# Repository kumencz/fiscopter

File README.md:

fiscopter
=========

Eagle: http://www.uloz.to/xudp2hTk/cadsoft-eagle-professional-6-5-0-patch-rar

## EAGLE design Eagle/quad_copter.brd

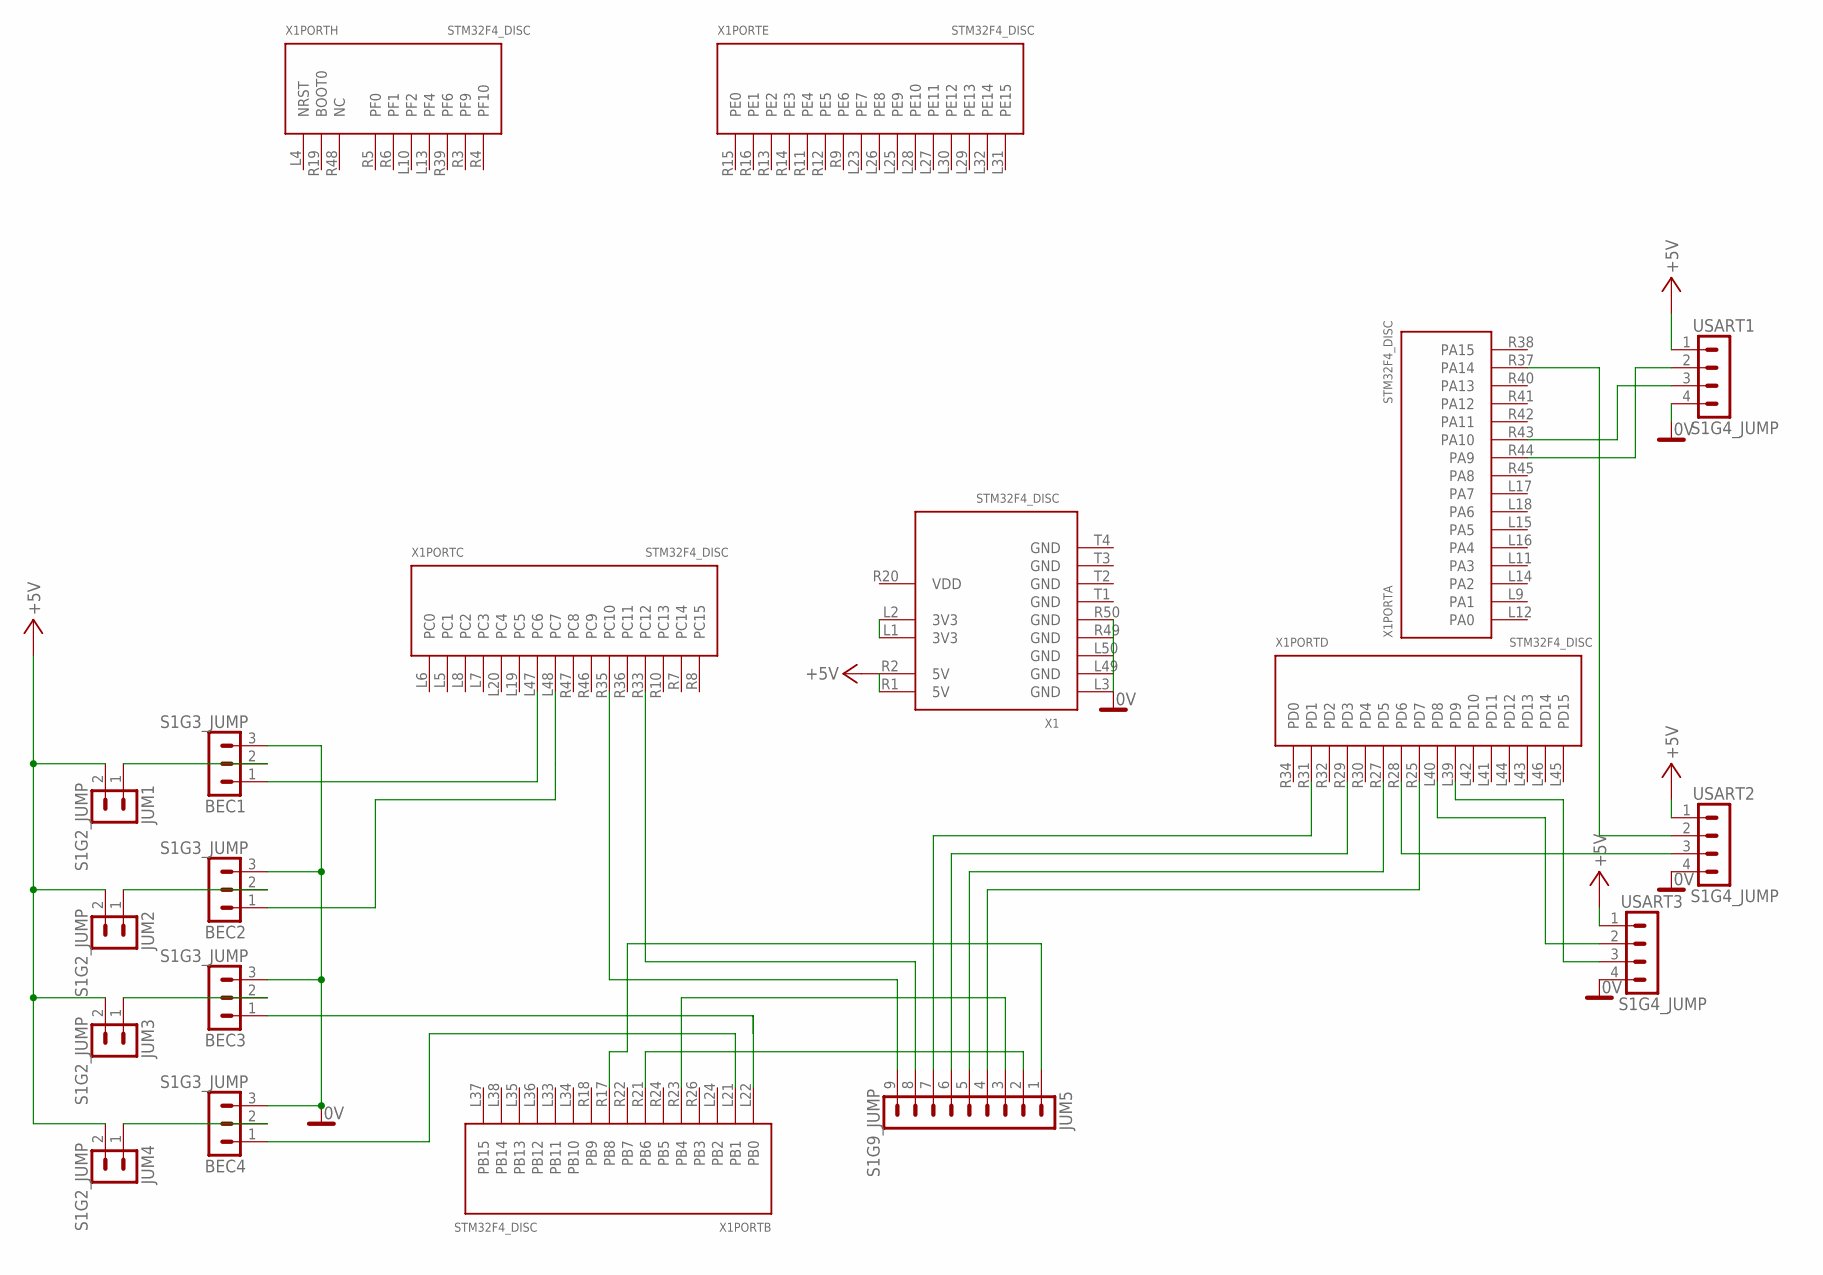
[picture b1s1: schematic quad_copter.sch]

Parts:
BEC1, BEC2, BEC3, BEC4: S1G3_JUMP; S1G3_JUM
JUM1, JUM2, JUM3, JUM4: S1G2_JUMP; S1G2_JUM
JUM5: S1G9_JUMP; S1G9_JUM
USART1, USART2, USART3: S1G4_JUMP; S1G4_JUM
X1: STM32F4_DISC

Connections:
0V: BEC1.3, BEC2.3, BEC3.3, BEC4.3, USART1.4, USART2.4, USART3.4, X1.L3 (GND), X1.L49 (GND), X1.L50 (GND), X1.R49 (GND), X1.R50 (GND)
+5V: JUM1.2, JUM2.2, JUM3.2, JUM4.2, USART1.1, USART2.1, USART3.1, X1.R1 (5V), X1.R2 (5V)
GND: X1.T1 (GND), X1.T2 (GND), X1.T3 (GND), X1.T4 (GND)
unnamed: USART3.3, X1.L39 (PD9)
unnamed: USART3.2, X1.L40 (PD8)
unnamed: USART1.2, X1.R44 (PA9)
unnamed: USART1.3, X1.R43 (PA10)
unnamed: USART2.2, X1.R37 (PA14)
unnamed: X1.L1 (3V3), X1.L2 (3V3)
unnamed: BEC4.2, JUM4.1
unnamed: BEC3.2, JUM3.1
unnamed: BEC2.2, JUM2.1
unnamed: BEC1.2, JUM1.1
unnamed: USART2.3, X1.R28 (PD6)
unnamed: BEC4.1, X1.L21 (PB1)
unnamed: BEC3.1, X1.L22 (PB0)
unnamed: BEC2.1, X1.L48 (PC7)
unnamed: BEC1.1, X1.L47 (PC6)
unnamed: JUM5.9, X1.R35 (PC10)
unnamed: JUM5.8, X1.R33 (PC12)
unnamed: JUM5.6, X1.R29 (PD3)
unnamed: JUM5.5, X1.R27 (PD5)
unnamed: JUM5.4, X1.R25 (PD7)
unnamed: JUM5.7, X1.R31 (PD1)
unnamed: JUM5.3, X1.R23 (PB4)
unnamed: JUM5.1, X1.R17 (PB8)
unnamed: JUM5.2, X1.R21 (PB6)
VDD: X1.R20 (VDD)

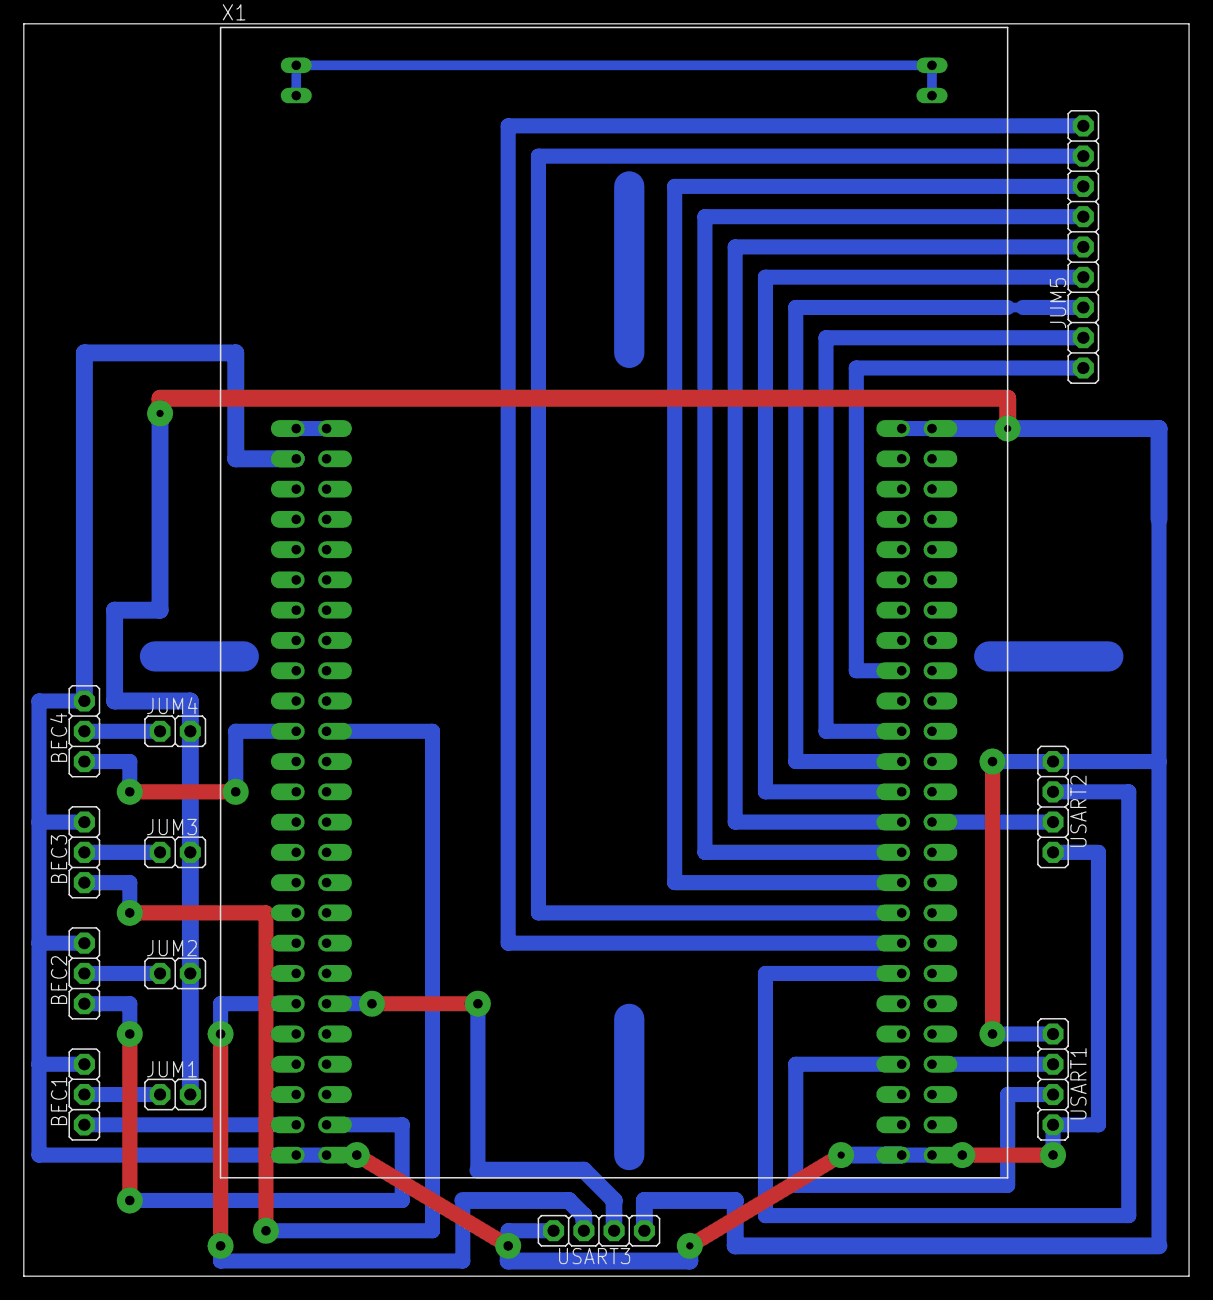
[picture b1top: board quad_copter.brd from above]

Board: 2 copper layers, 97.8 x 105.1 mm, 13 parts (0 on the bottom side), 27 nets.

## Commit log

2013-09-04 add eagle to readme
2013-09-04 first brd commit
2013-09-08 initial STM32F3-Discovery program
2013-09-11 added gyro + accelerometer
2013-10-07 new scheme and board
2013-11-05 Added Eagle stm32f3_disc library
2013-11-05 2nd version of board
2013-11-06 added new MDK project
2013-11-09 Added Processing programs
2013-11-12 STM code cleared
2013-11-12 Deleted old STM files
2013-11-12 ESC control
2013-11-13 Improved board layout
2013-11-19 Small cleaning in main.c and imu.c
2013-12-08 Added connector to board
2013-12-20 Remapped ESC pins to board
2013-12-29 Huge update
2013-12-29 Headers /comprimed/
2014-01-03 add .gitignore and libraries
2014-01-03 change regulator function (must be called periodicaly, PID is computed in dual axis, ...)
2014-01-03 add periodic timer and regulation of motors
2014-01-03 přehození motorů v regulátoru(přední vs zadní)
2014-01-04 Increased input array
2014-01-05 Code separation + graph print in second window
2014-01-05 Screenshots
2014-01-05 Half USART speed, read_imu in each 1 ms
2014-02-08 added one line in graph + lines table
2014-02-08 ranges update
2014-02-08 Imu update to +-180 + clearing
2014-02-08 updated .gitignore
2014-02-21 Change TX USART (add TX interupt and ring TX buffer) - NOT TESTED on HW
2014-02-21 add usart_protocol files
2014-02-22 Add ring buffer to USART RX, add first version of parse functions, old version of code in interupt from USART RX is comented
2014-02-23 Added USART3 as main USART
2014-03-04 repare tx site of usart, rx receive is OK, parse isn't
2014-03-09 funkční RX i TX
2014-03-09 updated to processing 2.1.1
2014-03-09 Connect to specific port
2014-03-09 Initial commit FlyControler for PC
2014-03-10 Change Rx ring buffer to Rx array ring buffer
2014-03-10 add RxParser
2014-03-11 Add support to PID and other commands
2014-03-12 Merge branch 'Dev_DISCOVERY'
    Conflicts:
    STM32F3-Discovery/Fiscopter/MDK-ARM/Fiscopter.uvopt
2014-03-14 Complete rx parser
2014-03-14 Add sender, add Rx and Tx messages Dictionaryes
2014-03-14 Add Live Controler
2014-03-14 add ESC_calibrate support
2014-03-14 add DataLog Output
2014-03-14 USART protocol clear
2014-03-14 change dataloger, liveControler, txSendder
2014-03-14 Change const type
2014-03-14 Warnings fix
2014-03-17 Add Debug Form
2014-03-17 Add DBG_PID
2014-03-17 Add motor RPM dbg show, set RPM command and ENABLE od DISABLE "CHECK_LIVE" send, chenge DBG_PID form (Anchor, onClosed, ...)
2014-03-17 Change GITIgnore
2014-03-17 add enable send DBG messages
2014-03-18 Add UniversalComunicator class
2014-03-18 Add support for use serial port in PC
2014-03-18 change DBG:form -> now comunicate via UniversalComunicator, not over dataLoger
2014-03-18 Changes in FlyControler and Discovery
2014-03-19 Debug PID is posible
2014-03-19 reipare P_SET_RPM
2014-03-24 Add total stop
2014-03-26 Change PID to motor conections, disable ESC output impuls width length < 0, add PID_SET confirm values
2014-03-26 [FLYCONTROLER]: Add Message K_PID_SETTED to parse function and show ths message in DBG_PID form
2014-03-28 repair FlyControler

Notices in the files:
parts and their libraries:
Copyright (C) PaJa 2011
Copyright (C) PaJa 2001-2011
